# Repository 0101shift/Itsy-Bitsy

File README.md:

# Itsy-Bitsy
A small LED pixel dot, which gets activated through an external IR interrupt.
By placing in an array, you can create various colourful LED colour patterns.

NOTE: DO NOT MOUNT U2 (comparator) while flashing the controller as it is used for ICSP programming.

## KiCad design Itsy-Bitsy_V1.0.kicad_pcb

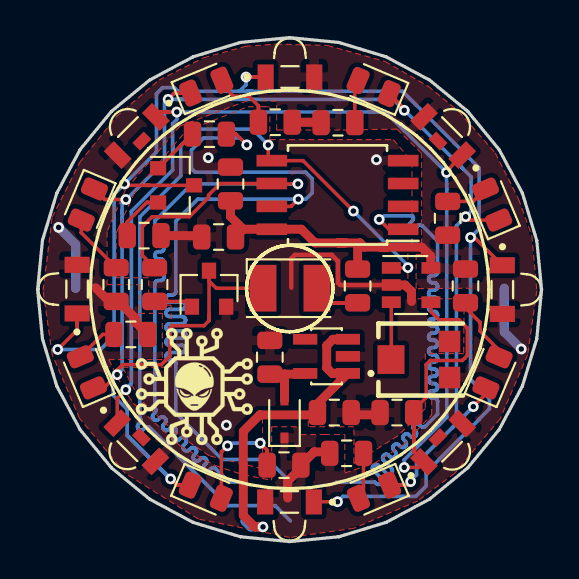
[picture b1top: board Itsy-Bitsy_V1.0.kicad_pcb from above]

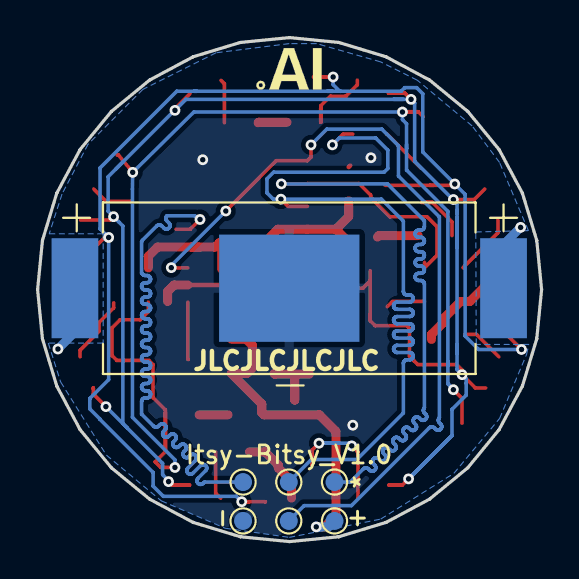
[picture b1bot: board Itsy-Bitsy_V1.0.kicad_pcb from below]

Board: 2 copper layers, 28.0 x 28.0 mm, 48 parts (7 on the bottom side), 24 nets.

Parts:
BT1: BC-2003; BAT_BC-2003
C1, C2: 1uf; C_0805_2012Metric
C3: 4.7uf; C_0805_2012Metric
C4: 0.1uf; C_0805_2012Metric
D1: AA3528LSECKT/J3; LED_PLCC-2
D2, D3, D4, D5: SFH_4045N; LED_SFH_4045N
D6, D7, D8, D9, D11, D12, D13, D14: green; LED_0805_2012Metric
D10: ZLLS410TA; D_SOD-323
Q1, Q2: BC847; SOT-23
Q3, Q4, Q5, Q6: PT12-21C_TR8; TRANS_PT12-21C_TR8
R1, R2, R6, R7, R8, R9, R12, R13, R14, R15: R; R_0805_2012Metric
R3, R5, R10: 10k; R_0805_2012Metric
R4: TC33X-2-103E
TP1, TP2, TP3, TP4, TP5, TP6: TestPoint; TestPoint_Pad_D1.0mm
U1: AP2112K-3.3TRG1
U2: TLV7031DBVR; SOT-23-5
U3: ATtiny85-20SU; SOIJ-8_5.3x5.3mm_P1.27mm

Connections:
/5V_in: C1.1, TP4.1, U1.1, U1.3
/comp_out_mosi: TP5.1, U2.1, U3.5
/ir_out_sck: R5.2, TP2.1, U3.7
/led_out_miso: R10.2, TP3.1, U3.6
/rst: TP1.1, U3.1
/sense_in: Q3.E, Q4.E, Q5.E, Q6.E, R3.2, U2.4
/vin: BT1.S1+, BT1.S2+, C3.1, C4.1, D2.2, D3.2, D4.2, D5.2, D10.1, Q3.C, Q4.C, Q5.C, Q6.C, R1.2, R4.1, R6.2, R7.2, R8.2, R9.2, R12.2, R13.2, R14.2, R15.2, U2.5, U3.8
GND: BT1.-, C1.2, C2.2, C3.2, C4.2, Q2.2, R2.1, R3.1, R4.3, TP6.1, U1.2, U2.2, U3.4
unnamed: C2.1, D10.2, U1.5
unnamed: D1.1, D6.1, D7.1, D8.1, D9.1, D11.1, D12.1, D13.1, D14.1, Q2.3
unnamed: D1.2, R1.1
unnamed: D2.1, D3.1, D4.1, D5.1, Q1.3
unnamed: D6.2, R12.1
unnamed: D7.2, R13.1
unnamed: D8.2, R14.1
unnamed: D9.2, R15.1
unnamed: D11.2, R6.1
unnamed: D12.2, R7.1
unnamed: D13.2, R8.1
unnamed: D14.2, R9.1
unnamed: Q1.1, R5.1
unnamed: Q1.2, R2.2
unnamed: Q2.1, R10.1
unnamed: R4.2, U2.3

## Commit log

2021-07-03 Add files via upload
    Added Itsy-Bitsy SCH, PCB and Gerber files
2021-07-03 Update README.md
    Added Itsy-Bitsy image and modified the readme.
2021-07-03 Update README.md
    modified the readme.
2021-07-03 Update README.md
    modified the Readme
2022-06-18 Update README.md
    Updated Image
2022-06-18 Add files via upload
    Added Project design file
2022-06-18 Update README.md
    Added Image
2022-06-20 Add files via upload
    Added Design in .pdf format
